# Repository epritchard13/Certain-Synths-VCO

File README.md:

Hello.
This is a project contributed to by Eddie Pritchard and Evan Gobien. Collectively, we are establishing an electronic synthesizer company.

Our project involves designing, prototyping, and manufacturing an 8-voice polyphonic euro rack standard synth that remains low cost.

Problem - Pure analog synths such as euro rack are expensive and have low functionality, cheaper alternatives with more functionality such as digital recreations of analog audio don't fully capture the pure raw sound you get from analog synths.

Our Solution - Designing a, fully analog, 8-voiced, euro rack compatible, low cost synth by optimizing space and circuit designs. Our designs are made for a wide variety of skill sets such as people who have never used modular synths before to industry professionals.

So far, we have built/are building the following components:

  - Low Noise 12 VAC to +/-12 VDC Power Supply
  - VCO

The following elements are currently in development:

  - VCA
  - LFO
  - ADSR
  - MIDI to CV 

If you have any questions or wish to learn more, please direct email to epritchard@vt.edu or ecgobien@gmail.com

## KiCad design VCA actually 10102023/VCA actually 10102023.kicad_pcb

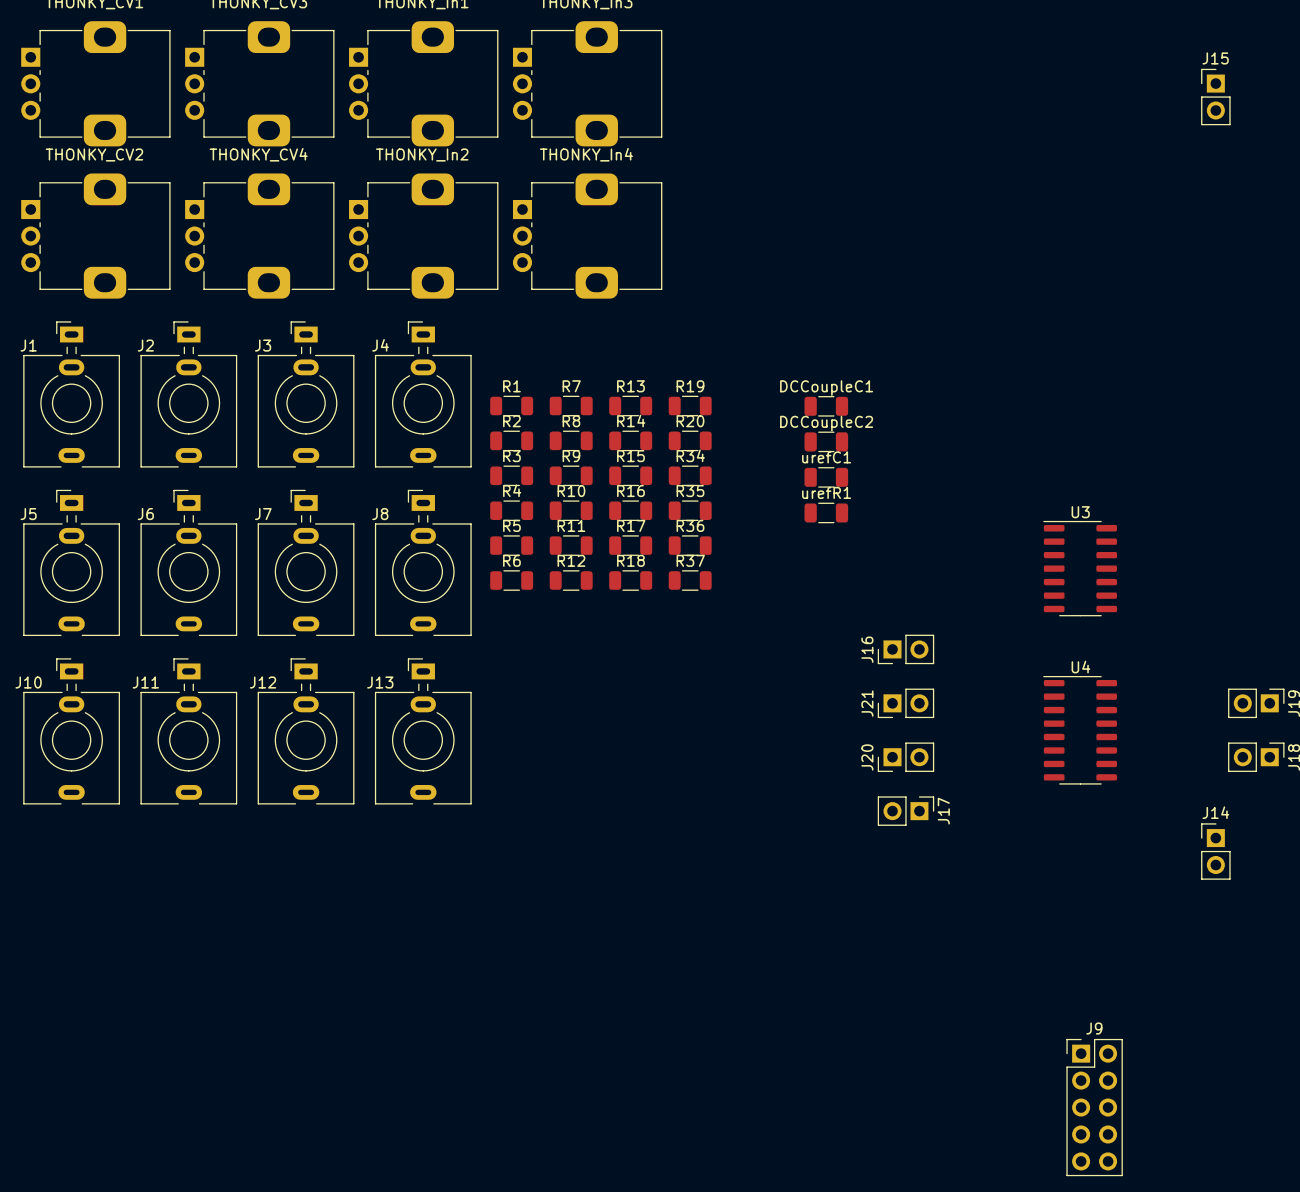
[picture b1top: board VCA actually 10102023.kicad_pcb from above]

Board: 2 copper layers, 59 parts (0 on the bottom side), 49 nets, no tracks yet.

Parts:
DCCoupleC1, DCCoupleC2: 0.1uF; C_1206_3216Metric
J1: Nigo Chanel Log; Jack_3.5mm_QingPu_WQP-PJ398SM_Vertical
J2: Niggo Chanel Log 2; Jack_3.5mm_QingPu_WQP-PJ398SM_Vertical
J3: Channel Log 3; Jack_3.5mm_QingPu_WQP-PJ398SM_Vertical
J4: Nigo Chanel Log 4; Jack_3.5mm_QingPu_WQP-PJ398SM_Vertical
J5: Out3; Jack_3.5mm_QingPu_WQP-PJ398SM_Vertical
J6: Out1; Jack_3.5mm_QingPu_WQP-PJ398SM_Vertical
J7: Out2; Jack_3.5mm_QingPu_WQP-PJ398SM_Vertical
J8: Out4; Jack_3.5mm_QingPu_WQP-PJ398SM_Vertical
J9: Conn_02x05_Counter_Clockwise; PinHeader_2x05_P2.54mm_Vertical
J10: In1; Jack_3.5mm_QingPu_WQP-PJ398SM_Vertical
J11: In2; Jack_3.5mm_QingPu_WQP-PJ398SM_Vertical
J12: In3; Jack_3.5mm_QingPu_WQP-PJ398SM_Vertical
J13: In4; Jack_3.5mm_QingPu_WQP-PJ398SM_Vertical
J14, J15, J16, J17, J18, J19, J20, J21: Conn_01x02; PinHeader_1x02_P2.54mm_Vertical
R1, R2, R3, R4, R5, R6, R7, R8, R9, R10, R11, R12, R13, R14, R15, R16: 47k; R_1206_3216Metric
R17, R18, R19, R20: 500k; R_1206_3216Metric
R34, R35, R36, R37: 1k; R_1206_3216Metric
THONKY_CV1, THONKY_CV2, THONKY_CV3, THONKY_CV4: 100k Pot; Potentiometer_Alps_RK09K_Single_Vertical
THONKY_In1, THONKY_In2, THONKY_In3, THONKY_In4: 100k Pot; Potentiometer_Alps_RK09K_Single_Vertical
U3: LM324; SOIC-14_3.9x8.7mm_P1.27mm
U4: 74LS138; SOIC-16_3.9x9.9mm_P1.27mm
urefC1: 5nF; C_1206_3216Metric
urefR1: 100; C_1206_3216Metric

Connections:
+12V: DCCoupleC1.2, J9.1, J9.10, R8.1, R11.1, R13.1, R16.1, R17.2, R18.2, R19.2, R20.2, U3.4 (V+), U4.16 (VCC)
-12V: DCCoupleC2.1, J9.5, J9.6, R9.2, R12.2, R14.2, R15.2, U3.11 (V-), U4.9 (O6)
GND: DCCoupleC1.1, DCCoupleC2.2, J1.S, J2.S, J3.S, J4.S, J5.S, J6.S, J7.S, J8.S, J9.2, J9.3, J9.4, J9.7, J9.8, J9.9, J10.S, J11.S, J12.S, J13.S, R1.1, R2.1, R3.1, R4.1, THONKY_CV1.3, THONKY_CV2.3, THONKY_CV3.3, THONKY_CV4.3, U4.8 (GND), urefC1.1
unnamed: J5.T, R36.2
unnamed: J6.T, R35.2
unnamed: J7.T, R34.2
unnamed: J8.T, R37.2
unnamed: J12.T, R5.1
unnamed: J13.T, R10.1
unnamed: J14.1, THONKY_In1.2
unnamed: J10.T, J14.2, R6.2
unnamed: J15.1, THONKY_In2.2
unnamed: J11.T, J15.2, R7.2
unnamed: J16.1, THONKY_In3.2
unnamed: J16.2, R5.2, U4.2 (A1)
unnamed: J17.1, R10.2, U4.7 (O7)
unnamed: J17.2, THONKY_In4.2
unnamed: J18.1, THONKY_CV1.2
unnamed: J1.T, J18.2, U4.11 (O4)
unnamed: J19.1, THONKY_CV2.2
unnamed: J2.T, J19.2, U4.14 (O1)
unnamed: J20.1, THONKY_CV4.2
unnamed: J4.T, J20.2, U4.6 (E3)
unnamed: J21.1, THONKY_CV3.2
unnamed: J3.T, J21.2, U4.3 (A2)
unnamed: R8.2, THONKY_In3.3
unnamed: R9.1, THONKY_In3.1
unnamed: R11.2, THONKY_In4.3
unnamed: R12.1, THONKY_In4.1
unnamed: R13.2, THONKY_In1.3
unnamed: R14.1, THONKY_In1.1
unnamed: R15.1, THONKY_In2.1
unnamed: R16.2, THONKY_In2.3
unnamed: R17.1, THONKY_CV2.1
unnamed: R18.1, THONKY_CV1.1
unnamed: R19.1, THONKY_CV4.1
unnamed: R20.1, THONKY_CV3.1
unnamed: R2.2, U3.3 (+), U4.5 (E2)
unnamed: R37.1, U3.1, U3.2 (-)
unnamed: R1.2, U3.5 (+), U4.4 (E1)
unnamed: R36.1, U3.6 (-), U3.7
unnamed: R4.2, U3.10 (+), U4.13 (O2)
unnamed: R34.1, U3.8, U3.9 (-)
unnamed: R3.2, U3.12 (+), U4.12 (O3)
unnamed: R35.1, U3.13 (-), U3.14
unnamed: U4.1 (A0), urefR1.2
unnamed: R7.1, U4.15 (O0)
unnamed: R6.1, U4.10 (O5)
unnamed: urefC1.2, urefR1.1

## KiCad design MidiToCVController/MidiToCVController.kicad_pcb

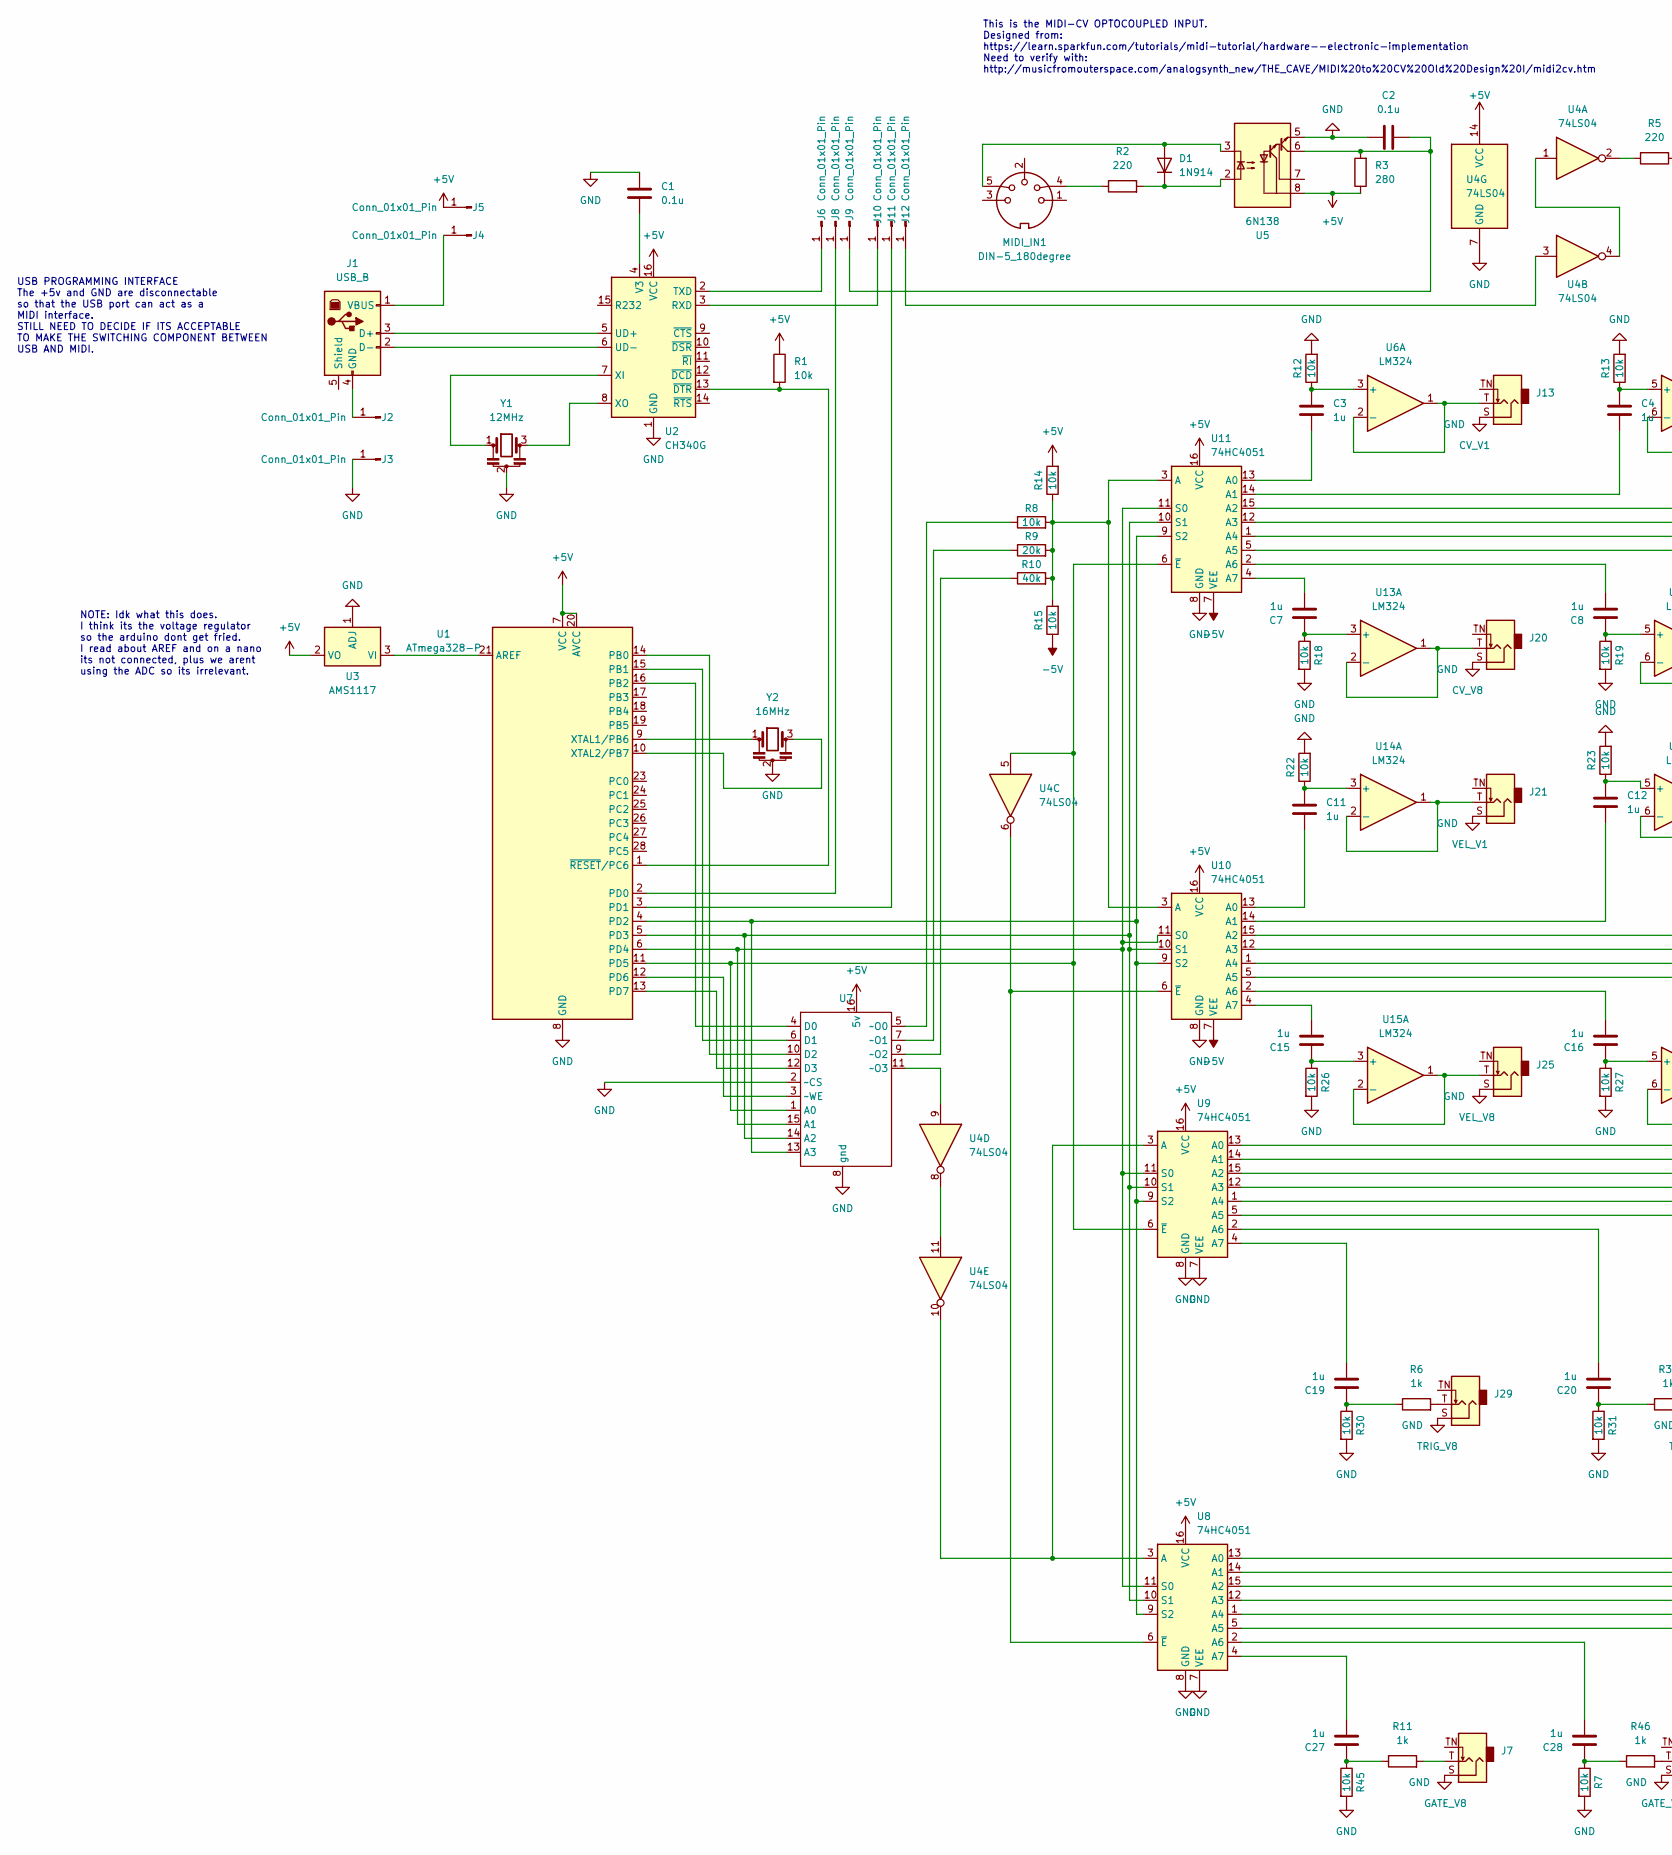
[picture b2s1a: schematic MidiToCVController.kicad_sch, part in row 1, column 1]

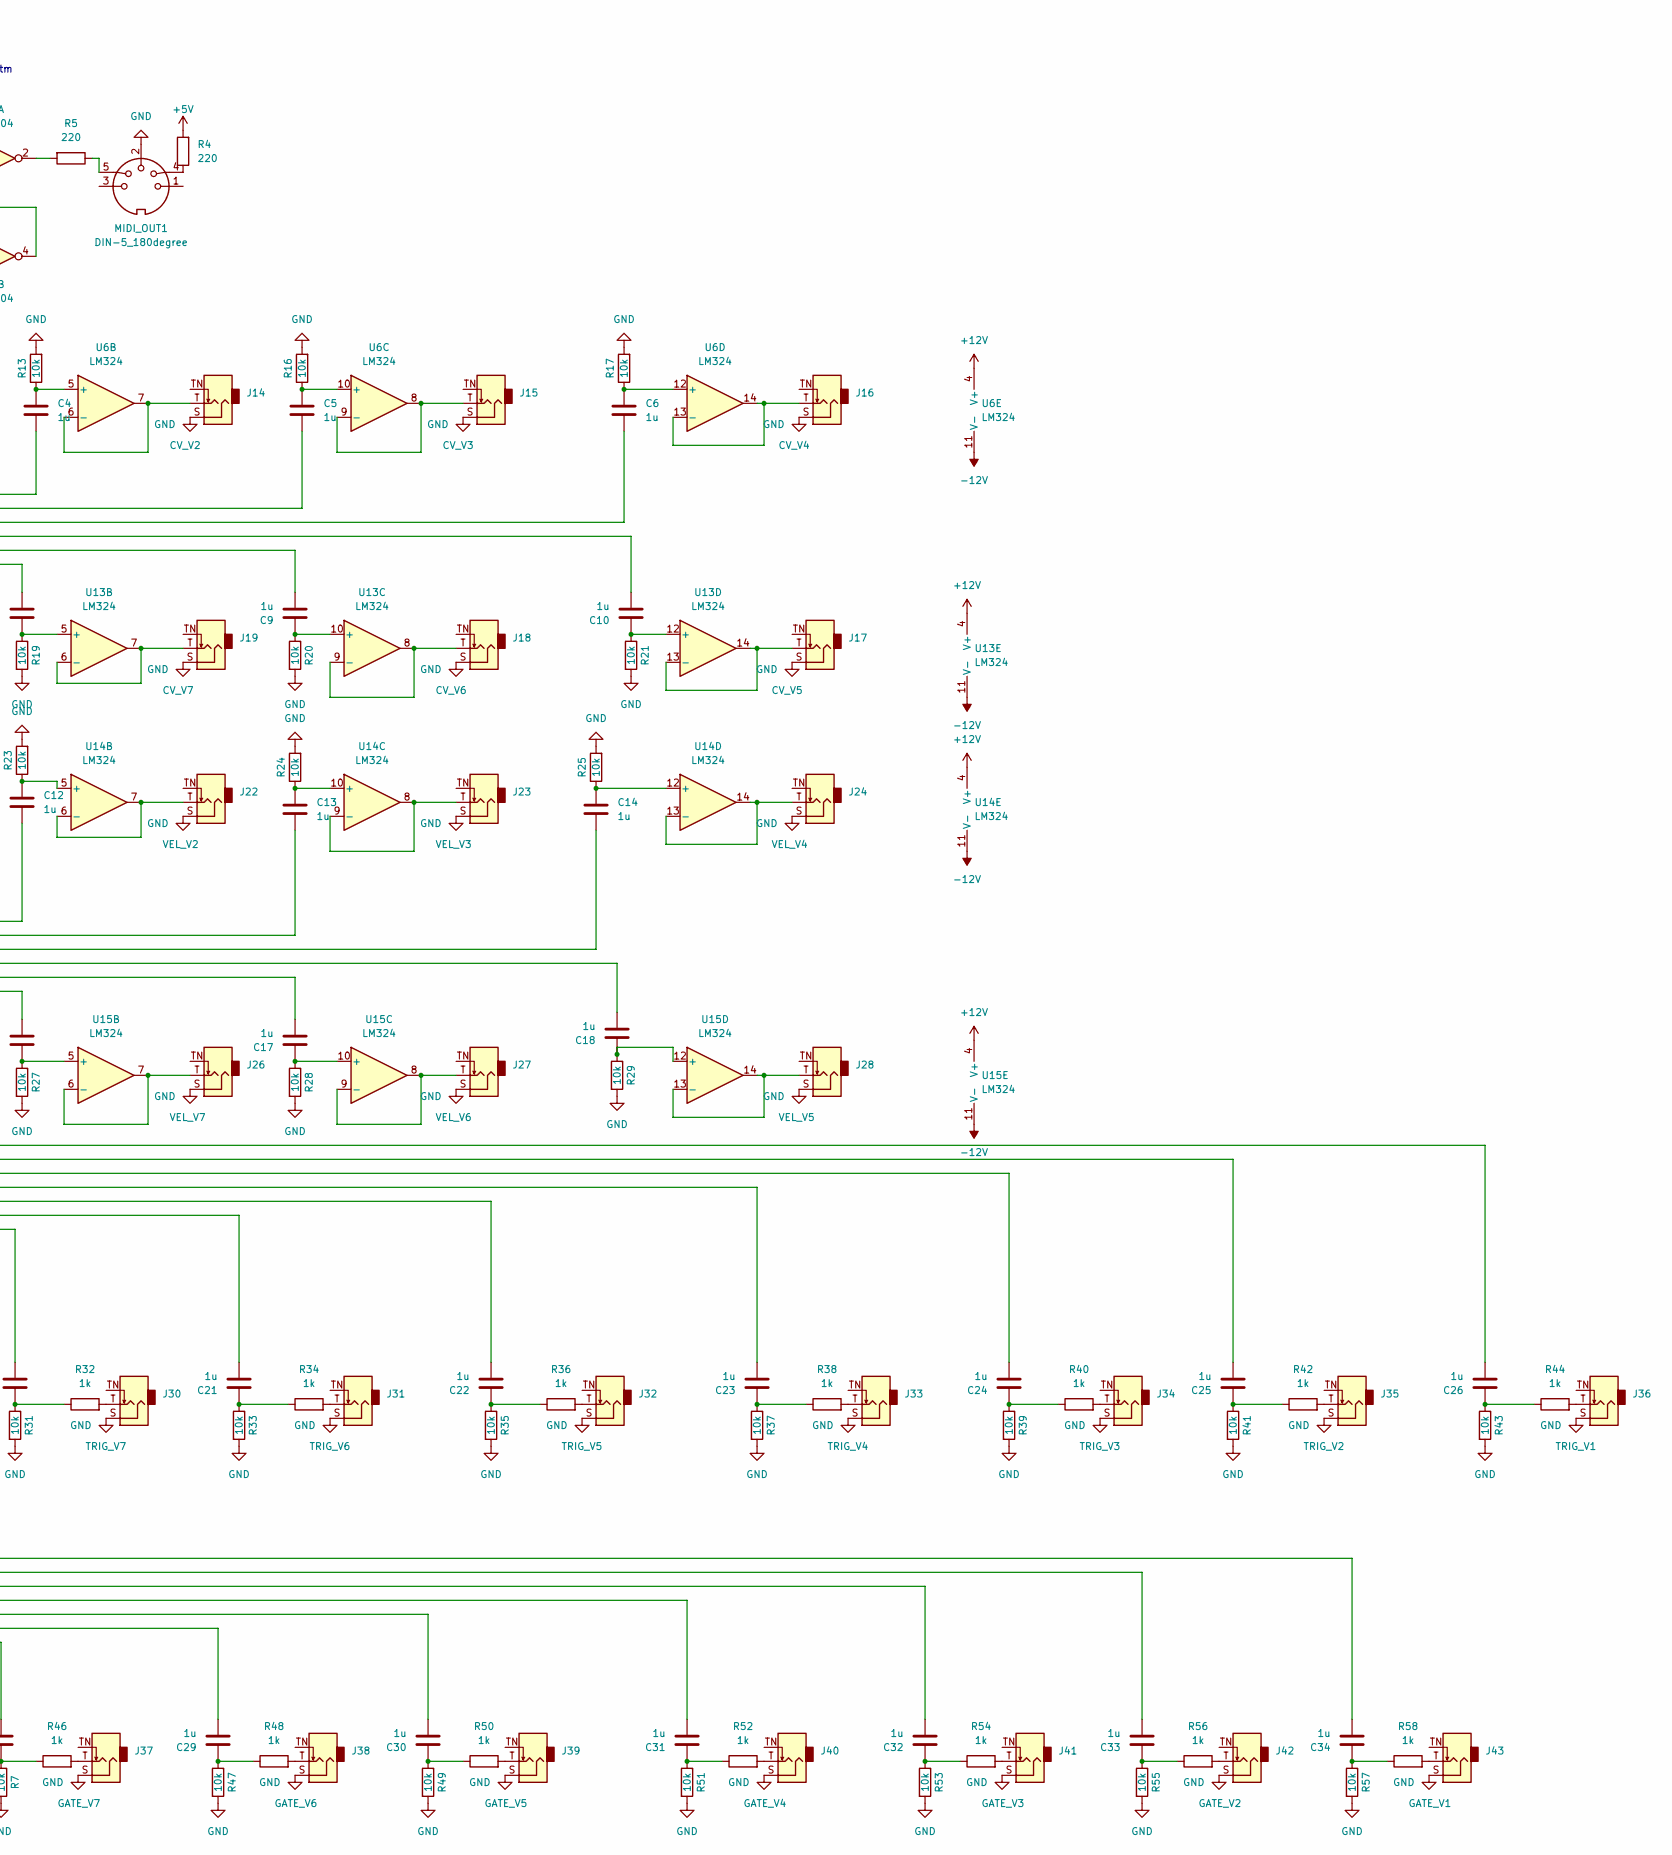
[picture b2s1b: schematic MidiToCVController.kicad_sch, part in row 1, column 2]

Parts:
C1, C2: 0.1u; C_1206_3216Metric
C3, C4, C5, C6, C7, C8, C9, C10, C11, C12, C13, C14, C15, C16, C17, C18, C19, C20, C21, C22, C23, C24, C25, C26, C27, C28, C29, C30, C31, C32, C33, C34: 1u; C_1206_3216Metric
D1: 1N914; D_DO-35_SOD27_P7.62mm_Horizontal
J1: USB_B; USB_B_TE_5787834_Vertical
J2, J3, J4, J5, J6, J8, J9, J10, J11, J12: Conn_01x01_Pin; PinHeader_1x01_P1.00mm_Vertical
J7: GATE_V8; Jack_3.5mm_QingPu_WQP-PJ398SM_Vertical
J13: CV_V1; Jack_3.5mm_QingPu_WQP-PJ398SM_Vertical
J14: CV_V2; Jack_3.5mm_QingPu_WQP-PJ398SM_Vertical
J15: CV_V3; Jack_3.5mm_QingPu_WQP-PJ398SM_Vertical
J16: CV_V4; Jack_3.5mm_QingPu_WQP-PJ398SM_Vertical
J17: CV_V5; Jack_3.5mm_QingPu_WQP-PJ398SM_Vertical
J18: CV_V6; Jack_3.5mm_QingPu_WQP-PJ398SM_Vertical
J19: CV_V7; Jack_3.5mm_QingPu_WQP-PJ398SM_Vertical
J20: CV_V8; Jack_3.5mm_QingPu_WQP-PJ398SM_Vertical
J21: VEL_V1; Jack_3.5mm_QingPu_WQP-PJ398SM_Vertical
J22: VEL_V2; Jack_3.5mm_QingPu_WQP-PJ398SM_Vertical
J23: VEL_V3; Jack_3.5mm_QingPu_WQP-PJ398SM_Vertical
J24: VEL_V4; Jack_3.5mm_QingPu_WQP-PJ398SM_Vertical
J25: VEL_V8; Jack_3.5mm_QingPu_WQP-PJ398SM_Vertical
J26: VEL_V7; Jack_3.5mm_QingPu_WQP-PJ398SM_Vertical
J27: VEL_V6; Jack_3.5mm_QingPu_WQP-PJ398SM_Vertical
J28: VEL_V5; Jack_3.5mm_QingPu_WQP-PJ398SM_Vertical
J29: TRIG_V8; Jack_3.5mm_QingPu_WQP-PJ398SM_Vertical
J30: TRIG_V7; Jack_3.5mm_QingPu_WQP-PJ398SM_Vertical
J31: TRIG_V6; Jack_3.5mm_QingPu_WQP-PJ398SM_Vertical
J32: TRIG_V5; Jack_3.5mm_QingPu_WQP-PJ398SM_Vertical
J33: TRIG_V4; Jack_3.5mm_QingPu_WQP-PJ398SM_Vertical
J34: TRIG_V3; Jack_3.5mm_QingPu_WQP-PJ398SM_Vertical
J35: TRIG_V2; Jack_3.5mm_QingPu_WQP-PJ398SM_Vertical
J36: TRIG_V1; Jack_3.5mm_QingPu_WQP-PJ398SM_Vertical
J37: GATE_V7; Jack_3.5mm_QingPu_WQP-PJ398SM_Vertical
J38: GATE_V6; Jack_3.5mm_QingPu_WQP-PJ398SM_Vertical
J39: GATE_V5; Jack_3.5mm_QingPu_WQP-PJ398SM_Vertical
J40: GATE_V4; Jack_3.5mm_QingPu_WQP-PJ398SM_Vertical
J41: GATE_V3; Jack_3.5mm_QingPu_WQP-PJ398SM_Vertical
J42: GATE_V2; Jack_3.5mm_QingPu_WQP-PJ398SM_Vertical
J43: GATE_V1; Jack_3.5mm_QingPu_WQP-PJ398SM_Vertical
MIDI_IN1: DIN-5_180degree; PinSocket_1x05_P2.00mm_Vertical
MIDI_OUT1: DIN-5_180degree; PinSocket_1x05_P2.00mm_Vertical
R1, R7, R8, R12, R13, R14, R15, R16, R17, R18, R19, R20, R21, R22, R23, R24, R25, R26, R27, R28, R29, R30, R31, R33, R35, R37, R39, R41, R43, R45, R47, R49, R51, R53, R55, R57: 10k; R_1206_3216Metric
R2, R4, R5: 220; R_1206_3216Metric
R3: 280; R_1206_3216Metric
R6, R11, R32, R34, R36, R38, R40, R42, R44, R46, R48, R50, R52, R54, R56, R58: 1k; R_1206_3216Metric
R9: 20k; R_1206_3216Metric
R10: 40k; R_1206_3216Metric
U1: ATmega328-P; TQFP-32_7x7mm_P0.8mm
U2: CH340G; SOIC-16_3.9x9.9mm_P1.27mm
U3: AMS1117; SOT-223-3_TabPin2
U4: 74LS04; DIP-14_W10.16mm
U5: 6N138; DIP-8_W7.62mm
U6, U13, U14, U15: LM324; DIP-14_W10.16mm
U7: DIP-16_W10.16mm
U8, U9, U10, U11: 74HC4051; DIP-16_W10.16mm
Y1: 12MHz; Oscillator_SMD_EuroQuartz_XO32-4Pin_3.2x2.5mm
Y2: 16MHz; Oscillator_SMD_EuroQuartz_XO32-4Pin_3.2x2.5mm

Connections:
+5V: J5.1, R1.1, R3.1, R4.2, R14.2, U1.7 (VCC), U1.20 (AVCC), U2.16 (VCC), U3.2 (VO), U4.14 (VCC), U5.8 (VCC), U7.16 (5v), U8.16 (VCC), U9.16 (VCC), U10.16 (VCC), U11.16 (VCC)
+12V: U6.4 (V+), U13.4 (V+), U14.4 (V+), U15.4 (V+)
-5V: R15.1, U10.7 (VEE), U11.7 (VEE)
-12V: U6.11 (V-), U13.11 (V-), U14.11 (V-), U15.11 (V-)
GND: C1.1, C2.1, J3.1, J7.S, J13.S, J14.S, J15.S, J16.S, J17.S, J18.S, J19.S, J20.S, J21.S, J22.S, J23.S, J24.S, J25.S, J26.S, J27.S, J28.S, J29.S, J30.S, J31.S, J32.S, J33.S, J34.S, J35.S, J36.S, J37.S, J38.S, J39.S, J40.S, J41.S, J42.S, J43.S, MIDI_OUT1.2, R7.2, R12.2, R13.2, R16.2, R17.2, R18.2, R19.2, R20.2, R21.2, R22.2, R23.2, R24.2, R25.2, R26.2, R27.2, R28.2, R29.2, R30.2, R31.2, R33.2, R35.2, R37.2, R39.2, R41.2, R43.2, R45.2, R47.2, R49.2, R51.2, R53.2, R55.2, R57.2, U1.8 (GND), U1.22 (GND), U2.1 (GND), U3.1 (ADJ), U4.7 (GND), U5.5 (GND), U7.2 (~CS), U7.8 (gnd), U8.7 (VEE), U8.8 (GND), U9.7 (VEE), U9.8 (GND), U10.8 (GND), U11.8 (GND), Y1.2, Y2.2
unnamed: C19.1, R6.1, R30.1
unnamed: C20.1, R31.1, R32.1
unnamed: C21.1, R33.1, R34.1
unnamed: C22.1, R35.1, R36.1
unnamed: C23.1, R37.1, R38.1
unnamed: C24.1, R39.1, R40.1
unnamed: C25.1, R41.1, R42.1
unnamed: C26.1, R43.1, R44.1
unnamed: C27.1, R11.1, R45.1
unnamed: C28.1, R7.1, R46.1
unnamed: C29.1, R47.1, R48.1
unnamed: C30.1, R49.1, R50.1
unnamed: C31.1, R51.1, R52.1
unnamed: C32.1, R53.1, R54.1
unnamed: C33.1, R55.1, R56.1
unnamed: C34.1, R57.1, R58.1
unnamed: D1.2 (A), MIDI_IN1.5, U5.3 (C2)
unnamed: D1.1 (K), R2.2, U5.2 (C1)
unnamed: J1.3 (D+), U2.5 (UD+)
unnamed: J1.2 (D-), U2.6 (UD-)
unnamed: J1.4 (GND), J2.1
unnamed: J1.1 (VBUS), J4.1
unnamed: J6.1, U2.2 (TXD)
unnamed: J7.T, R11.2
unnamed: J8.1, U1.2 (PD0)
unnamed: C2.2, J9.1, R3.2, U5.6 (VO2)
unnamed: J10.1, U2.3 (RXD)
unnamed: J11.1, U1.3 (PD1)
unnamed: J12.1, U4.3
unnamed: J29.T, R6.2
unnamed: J30.T, R32.2
unnamed: J31.T, R34.2
unnamed: J32.T, R36.2
unnamed: J33.T, R38.2
unnamed: J34.T, R40.2
unnamed: J35.T, R42.2
unnamed: J36.T, R44.2
unnamed: J37.T, R46.2
unnamed: J38.T, R48.2
unnamed: J39.T, R50.2
unnamed: J40.T, R52.2
unnamed: J41.T, R54.2
unnamed: J42.T, R56.2
unnamed: J43.T, R58.2
unnamed: MIDI_IN1.4, R2.1
unnamed: MIDI_OUT1.4, R4.1
unnamed: MIDI_OUT1.5, R5.1
unnamed: R5.2, U4.2
unnamed: U1.21 (AREF), U3.3 (VI)
unnamed: U1.14 (PB0), U7.10 (D2)
unnamed: U1.15 (PB1), U7.6 (D1)
unnamed: U1.16 (PB2), U7.4 (D0)
unnamed: U1.4 (PD2), U7.13 (A3), U8.9 (S2), U9.9 (S2), U10.9 (S2), U11.9 (S2)
unnamed: U1.5 (PD3), U7.14 (A2), U8.10 (S1), U9.10 (S1), U10.10 (S1), U11.10 (S1)
unnamed: U1.6 (PD4), U7.15 (A1), U8.11 (S0), U9.11 (S0), U10.11 (S0), U11.11 (S0)
unnamed: U1.11 (PD5), U4.5, U7.1 (A0), U9.6 (~E), U11.6 (~E)
unnamed: U1.12 (PD6), U7.3 (~WE)
unnamed: U1.13 (PD7), U7.12 (D3)
unnamed: U1.9 (XTAL1/PB6), Y2.1
unnamed: U1.10 (XTAL2/PB7), Y2.3
unnamed: R1.2, U1.1 (~RESET/PC6), U2.13 (~DTR)
unnamed: C1.2, U2.4 (V3)
unnamed: U2.7 (XI), Y1.1
unnamed: U2.8 (XO), Y1.3
unnamed: U4.1, U4.4
unnamed: U4.8, U4.11
unnamed: C3.1, R12.1, U6.3 (+)
unnamed: J13.T, U6.1, U6.2 (-)
unnamed: C4.1, R13.1, U6.5 (+)
unnamed: J14.T, U6.6 (-), U6.7
unnamed: C5.1, R16.1, U6.10 (+)
unnamed: J15.T, U6.8, U6.9 (-)
unnamed: C6.1, R17.1, U6.12 (+)
unnamed: J16.T, U6.13 (-), U6.14
unnamed: R8.1, U7.5 (~O0)
unnamed: R9.1, U7.7 (~O1)
unnamed: R10.1, U7.9 (~O2)
unnamed: U4.9, U7.11 (~O3)
unnamed: C34.2, U8.13 (A0)
unnamed: C33.2, U8.14 (A1)
unnamed: C32.2, U8.15 (A2)
unnamed: C31.2, U8.12 (A3)
unnamed: C30.2, U8.1 (A4)
unnamed: C29.2, U8.5 (A5)
unnamed: C28.2, U8.2 (A6)
unnamed: C27.2, U8.4 (A7)
unnamed: U4.10, U8.3 (A), U9.3 (A)
unnamed: C26.2, U9.13 (A0)
unnamed: C25.2, U9.14 (A1)
unnamed: C24.2, U9.15 (A2)
unnamed: C23.2, U9.12 (A3)
unnamed: C22.2, U9.1 (A4)
unnamed: C21.2, U9.5 (A5)
unnamed: C20.2, U9.2 (A6)
unnamed: C19.2, U9.4 (A7)
unnamed: C11.2, U10.13 (A0)
unnamed: C12.2, U10.14 (A1)
unnamed: C13.2, U10.15 (A2)
unnamed: C14.2, U10.12 (A3)
unnamed: C18.2, U10.1 (A4)
unnamed: C17.2, U10.5 (A5)
unnamed: C16.2, U10.2 (A6)
unnamed: C15.2, U10.4 (A7)
unnamed: R8.2, R9.2, R10.2, R14.1, R15.2, U10.3 (A), U11.3 (A)
unnamed: U4.6, U8.6 (~E), U10.6 (~E)
unnamed: C3.2, U11.13 (A0)
unnamed: C4.2, U11.14 (A1)
unnamed: C5.2, U11.15 (A2)
unnamed: C6.2, U11.12 (A3)
unnamed: C10.2, U11.1 (A4)
unnamed: C9.2, U11.5 (A5)
unnamed: C8.2, U11.2 (A6)
unnamed: C7.2, U11.4 (A7)
unnamed: C7.1, R18.1, U13.3 (+)
unnamed: J20.T, U13.1, U13.2 (-)
unnamed: C8.1, R19.1, U13.5 (+)
unnamed: J19.T, U13.6 (-), U13.7
unnamed: C9.1, R20.1, U13.10 (+)
unnamed: J18.T, U13.8, U13.9 (-)
unnamed: C10.1, R21.1, U13.12 (+)
unnamed: J17.T, U13.13 (-), U13.14
unnamed: C11.1, R22.1, U14.3 (+)
unnamed: J21.T, U14.1, U14.2 (-)
unnamed: C12.1, R23.1, U14.5 (+)
unnamed: J22.T, U14.6 (-), U14.7
unnamed: C13.1, R24.1, U14.10 (+)
unnamed: J23.T, U14.8, U14.9 (-)
unnamed: C14.1, R25.1, U14.12 (+)
unnamed: J24.T, U14.13 (-), U14.14
unnamed: C15.1, R26.1, U15.3 (+)
unnamed: J25.T, U15.1, U15.2 (-)
unnamed: C16.1, R27.1, U15.5 (+)
unnamed: J26.T, U15.6 (-), U15.7
unnamed: C17.1, R28.1, U15.10 (+)
unnamed: J27.T, U15.8, U15.9 (-)
unnamed: C18.1, R29.1, U15.12 (+)
unnamed: J28.T, U15.13 (-), U15.14

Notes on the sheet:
NOTE: Idk what this does. I think its the voltage regulator so the arduino dont get fried. I read about AREF and on a nano its not connected, plus we arent using the ADC so its irrelevant.
USB PROGRAMMING INTERFACE The +5v and GND are disconnectable so that the USB port can act as a MIDI interface. STILL NEED TO DECIDE IF ITS ACCEPTABLE TO MAKE THE SWITCHING COMPONENT BETWEEN USB AND MIDI.
This is the MIDI-CV OPTOCOUPLED INPUT. Designed from: https://learn.sparkfun.com/tutorials/midi-tutorial/hardware--electronic-implementation Need to verify with: http://musicfromouterspace.com/analogsynth_new/THE_CAVE/MIDI%20to%20CV%20Old%20Design%20I/midi2cv.htm

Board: 2 copper layers, 154 parts (0 on the bottom side), 142 nets, no tracks yet.

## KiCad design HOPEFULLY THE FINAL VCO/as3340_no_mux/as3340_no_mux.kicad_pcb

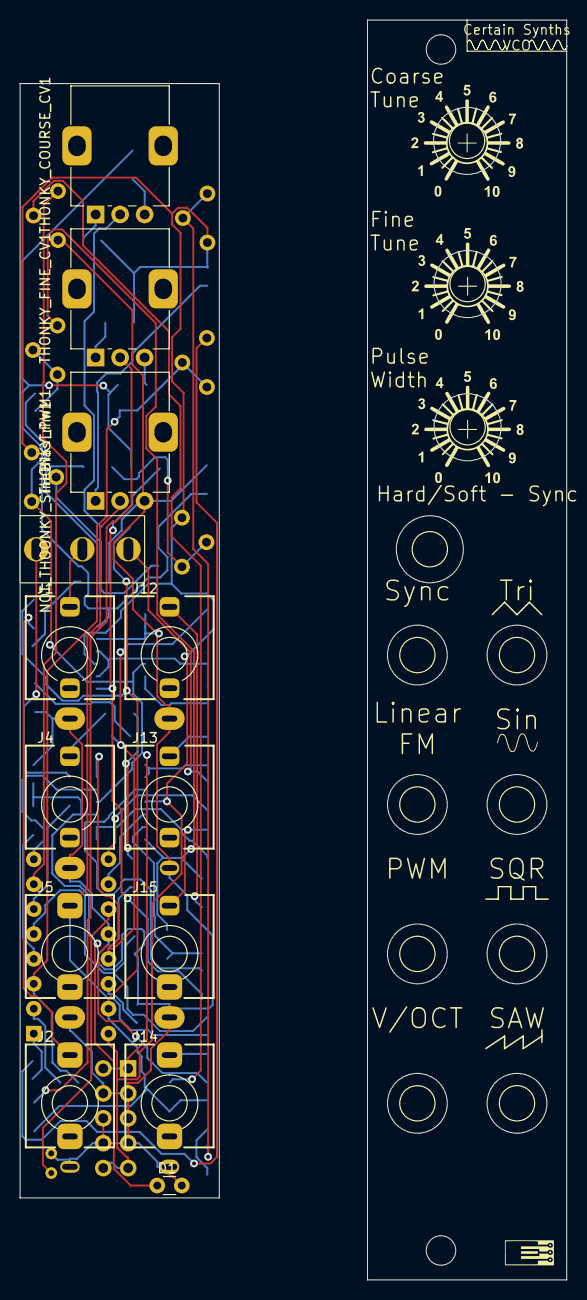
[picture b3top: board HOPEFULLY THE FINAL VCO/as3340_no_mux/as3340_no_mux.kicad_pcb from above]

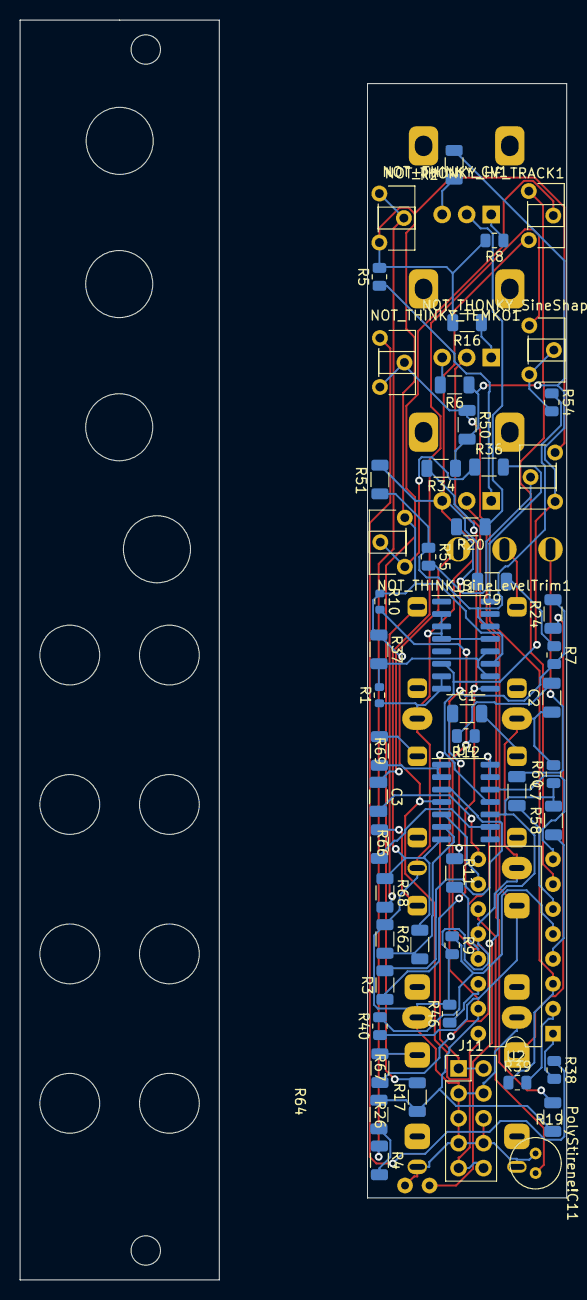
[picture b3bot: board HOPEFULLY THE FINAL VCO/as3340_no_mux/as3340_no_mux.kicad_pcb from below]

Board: 2 copper layers, 20.3 x 113.7 mm, 78 parts (53 on the bottom side), 55 nets.

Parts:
C1: 100nf; C_1206_3216Metric
C2, C9: 10nf; C_1206_3216Metric
C3, C7: 1nf; C_1206_3216Metric
D1: DIODE; C_Disc_D3.0mm_W1.6mm_P2.50mm
J1: Sync INput; Jack_3.5mm_QingPu_WQP-PJ398SM_Vertical
J2: CV1; Jack_3.5mm_QingPu_WQP-PJ398SM_Vertical
J4: LinearFmINput; Jack_3.5mm_QingPu_WQP-PJ398SM_Vertical
J5: PWM INput; Jack_3.5mm_QingPu_WQP-PJ398SM_Vertical
J11: Conn_02x05_Odd_Even; PinHeader_2x05_P2.54mm_Vertical
J12: TRI OUt; Jack_3.5mm_QingPu_WQP-PJ398SM_Vertical
J13: SIN OUT; Jack_3.5mm_QingPu_WQP-PJ398SM_Vertical
J14: SAW OUt; Jack_3.5mm_QingPu_WQP-PJ398SM_Vertical
J15: SQR OUT; Jack_3.5mm_QingPu_WQP-PJ398SM_Vertical
NOT+THINKY_CV1: 100k TrimPot; Potentiometer_ACP_CA6-H2,5_Horizontal
NOT_THINKY_TEMKO1: 10k Pot; Potentiometer_ACP_CA6-H2,5_Horizontal
NOT_THINK_SineLevelTrim1: 1M Pot; Potentiometer_ACP_CA6-H2,5_Horizontal
NOT_THONKY_HF_TRACK1: 10k Pot; Potentiometer_ACP_CA6-H2,5_Horizontal
NOT_THONKY_SineShapeTrim1: 100k Pot; Potentiometer_ACP_CA6-H2,5_Horizontal
NOT_THOONKY_SineBiasTrim1: 100k Pot; Potentiometer_ACP_CA6-H2,5_Horizontal
PolyStirene!C11: 1nf; C_Radial_D5.0mm_H5.0mm_P2.00mm
R1: 130k; R_0603_1608Metric
R2: 10k; R_1206_3216Metric
R3, R51, R66, R67, R68, R69: 1k; R_1206_3216Metric
R4, R6, R16, R20, R24, R26, R36, R62, R64: 100k; R_1206_3216Metric
R5: 20K; R_0805_2012Metric
R7, R12: 470; R_0805_2012Metric
R8, R9, R40, R60: 47k; R_0805_2012Metric
R10: 1.5M; R_0603_1608Metric
R11, R17, R19, R37: 1M; R_1206_3216Metric
R34: 4.7k; R_1206_3216Metric
R38: 24k; R_0805_2012Metric
R39: 5.6k; R_0805_2012Metric
R46: 1.8k; R_0805_2012Metric
R50: 910; R_1206_3216Metric
R54: 20k; R_0805_2012Metric
R55: 470k; R_0805_2012Metric
R58: 2k; R_1206_3216Metric
SLOTMAN: CV1; Jack_3.5mm_QingPu_WQP-PJ398SM_Vertical
SLOTMAN#2, SLOTMAN#3, SLOTMAN#4: CV1; Jack_3.5mm_QingPu_WQP-PJ398SM_Vertical
SW1: SW_SPDT; Dailywell mini DWB1 SPDT
Slot1, Slot2, Slot3, Slot4, Slot9, Slot10, Slot33, Slot87: CV1; Jack_3.5mm_QingPu_WQP-PJ398SM_Vertical
THONKY_COURSE_CV1: 100k Pot; Potentiometer_Alps_RK09K_Single_Vertical
THONKY_FINE_CV1: 100k Pot; Potentiometer_Alps_RK09K_Single_Vertical
THONKY_PWM1: 100k Pot; Potentiometer_Alps_RK09K_Single_Vertical
U1: LM13700; SOIC-16_3.9x9.9mm_P1.27mm
U2: AS3340; DIP-16_W7.62mm
U4: LM324; SOIC-14_3.9x8.7mm_P1.27mm

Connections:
+15V: J11.9, J11.10, NOT+THINKY_CV1.3, NOT_THINK_SineLevelTrim1.3, NOT_THOONKY_SineBiasTrim1.3, R5.2, R8.2, R10.1, R16.2, R37.1, U1.11 (V+), U2.16 (VCC), U4.4 (V+)
-15V: J11.1, J11.2, NOT_THOONKY_SineBiasTrim1.1, R2.1, R6.1, R34.1, R50.2, U1.6 (V-), U4.11 (V-)
GND: C2.1, C9.2, D1.1 (K), J1.S, J2.S, J4.S, J5.S, J11.3, J11.4, J11.5, J11.6, J11.7, J11.8, J12.S, J13.S, J14.S, J15.S, NOT_THONKY_HF_TRACK1.3, PolyStirene!C11.1, R1.1, R9.2, R46.2, R51.1, R60.2, R62.1, THONKY_PWM1.3, U1.2 (DIODE_BIAS), U1.3 (+), U1.4 (-), U1.7, U1.8, U1.13 (-), U2.12 (GND)
unnamed: C1.1, R11.1
unnamed: C1.2, J4.T
unnamed: C2.2, R12.2
unnamed: C9.1, R7.1
unnamed: D1.2 (A), R58.2, R60.1, U4.10 (+)
unnamed: J2.T, R24.1
unnamed: J5.T, R40.1, THONKY_PWM1.2
unnamed: J12.T, R68.2
unnamed: J13.T, R69.2
unnamed: J14.T, R67.2
unnamed: J15.T, R66.2
unnamed: NOT+THINKY_CV1.1, NOT+THINKY_CV1.2, R4.1
unnamed: NOT_THINKY_TEMKO1.1, R38.1
unnamed: NOT_THINK_SineLevelTrim1.1, NOT_THINK_SineLevelTrim1.2, R36.1
unnamed: NOT_THONKY_HF_TRACK1.2, R17.2
unnamed: NOT_THONKY_SineShapeTrim1.1, R64.2, R68.1, U4.7
unnamed: NOT_THONKY_SineShapeTrim1.2, NOT_THONKY_SineShapeTrim1.3, R54.2
unnamed: NOT_THOONKY_SineBiasTrim1.2, R55.2
unnamed: R1.2, R37.2, U1.10, U1.12
unnamed: R2.2, THONKY_COURSE_CV1.3
unnamed: R3.1, R34.2, U1.9
unnamed: R5.1, THONKY_PWM1.1
unnamed: R6.2, THONKY_FINE_CV1.3
unnamed: R8.1, THONKY_COURSE_CV1.1
unnamed: R16.1, THONKY_FINE_CV1.1
unnamed: R19.1, THONKY_FINE_CV1.2
unnamed: R20.1, THONKY_COURSE_CV1.2
unnamed: R4.2, R26.1
unnamed: R36.2, U1.16
unnamed: C7.1, SW1.1 (A)
unnamed: J1.T, SW1.2 (B)
unnamed: C3.1, SW1.3 (C)
unnamed: R51.2, R54.1, R55.1, U1.14 (+)
unnamed: PolyStirene!C11.2, U2.11 (CAP)
unnamed: R38.2, U2.1 (SCALE1)
unnamed: R39.2, U2.2 (SCALE2)
unnamed: NOT_THINKY_TEMKO1.2, NOT_THINKY_TEMKO1.3, R39.1, R50.1, U2.3 (VEE)
unnamed: R7.2, R17.1, R19.2, R20.2, R24.2, R26.2, U2.15 (VFCI)
unnamed: NOT_THONKY_HF_TRACK1.1, U2.7 (VHFT)
unnamed: C7.2, U2.6 (VHSI)
unnamed: R10.2, R11.2, R12.1, U2.13 (VLFI)
unnamed: R58.1, U2.4 (VP)
unnamed: R9.1, R40.2, U2.5 (VPWM)
unnamed: R46.1, U2.14 (VS)
unnamed: U2.8 (VSO), U4.12 (+)
unnamed: C3.2, U2.9 (VSSI)
unnamed: U2.10 (VTO), U4.5 (+)
unnamed: R3.2, U4.3 (+)
unnamed: R69.1, U4.1, U4.2 (-)
unnamed: R62.2, R64.1, U4.6 (-)
unnamed: R66.1, U4.8, U4.9 (-)
unnamed: R67.1, U4.13 (-), U4.14
